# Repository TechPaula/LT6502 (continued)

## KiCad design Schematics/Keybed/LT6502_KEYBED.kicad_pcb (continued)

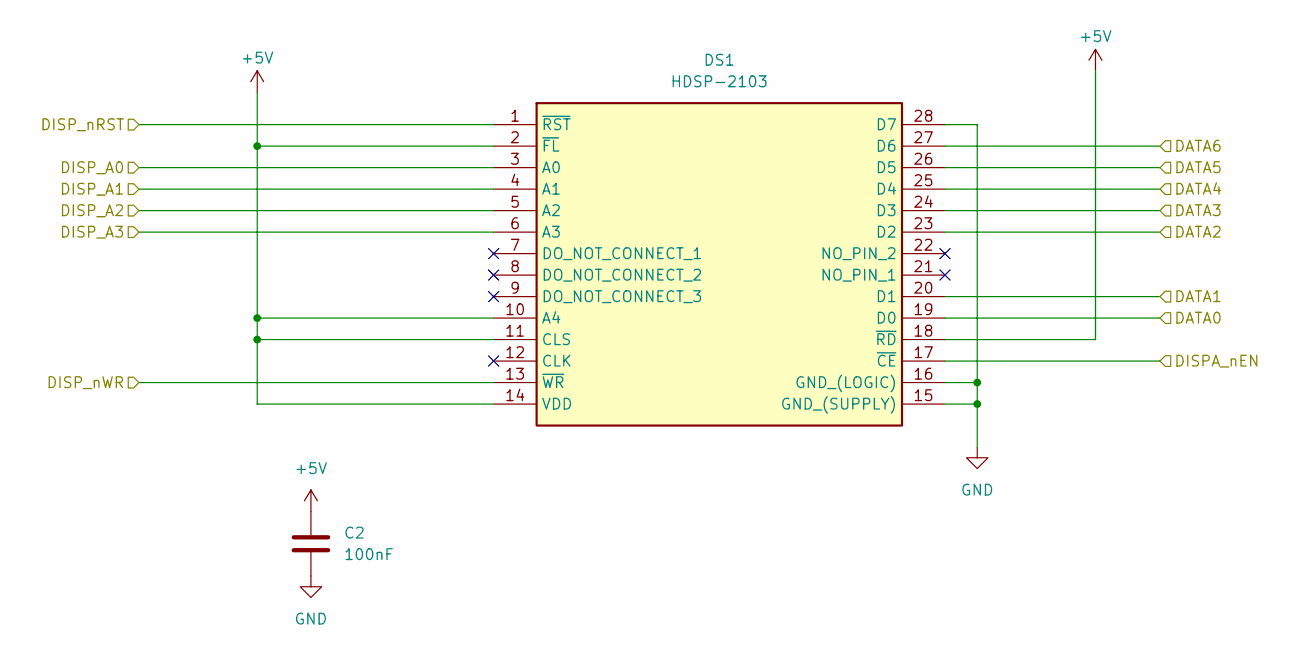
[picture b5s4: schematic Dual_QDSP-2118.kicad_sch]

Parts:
C2: 100nF; C_0805_2012Metric; LCSC C49678
DS1: HDSP-2103; DIPS1524W64P254L7087H685Q28N; Manufacturer_Part_Number HDSP-2503; Mouser Part Number 630-HDSP-2503

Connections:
+5V: C2.1, DS1.2 (~FL), DS1.10 (A4), DS1.11 (CLS), DS1.14 (VDD), DS1.18 (~RD); also elsewhere on the board
/DISPLAYs/DATA0: DS1.19 (D0); also elsewhere on the board
/DISPLAYs/DATA1: DS1.20 (D1); also elsewhere on the board
/DISPLAYs/DATA2: DS1.23 (D2); also elsewhere on the board
/DISPLAYs/DATA3: DS1.24 (D3); also elsewhere on the board
/DISPLAYs/DATA4: DS1.25 (D4); also elsewhere on the board
/DISPLAYs/DATA5: DS1.26 (D5); also elsewhere on the board
/DISPLAYs/DATA6: DS1.27 (D6); also elsewhere on the board
/DISPLAYs/DISPA_nEN: DS1.17 (~CE); also elsewhere on the board
/DISPLAYs/DISP_nRST: DS1.1 (~RST); also elsewhere on the board
/DISPLAYs/DISP_nWR: DS1.13 (~WR); also elsewhere on the board
AVR_TDO: DS1.6 (A3); also elsewhere on the board
DISP_A0: DS1.3 (A0); also elsewhere on the board
DISP_A1: DS1.4 (A1); also elsewhere on the board
DISP_A2: DS1.5 (A2); also elsewhere on the board
GND: C2.2, DS1.15 (GND_(SUPPLY)), DS1.16 (GND_(LOGIC)), DS1.28 (D7); also elsewhere on the board

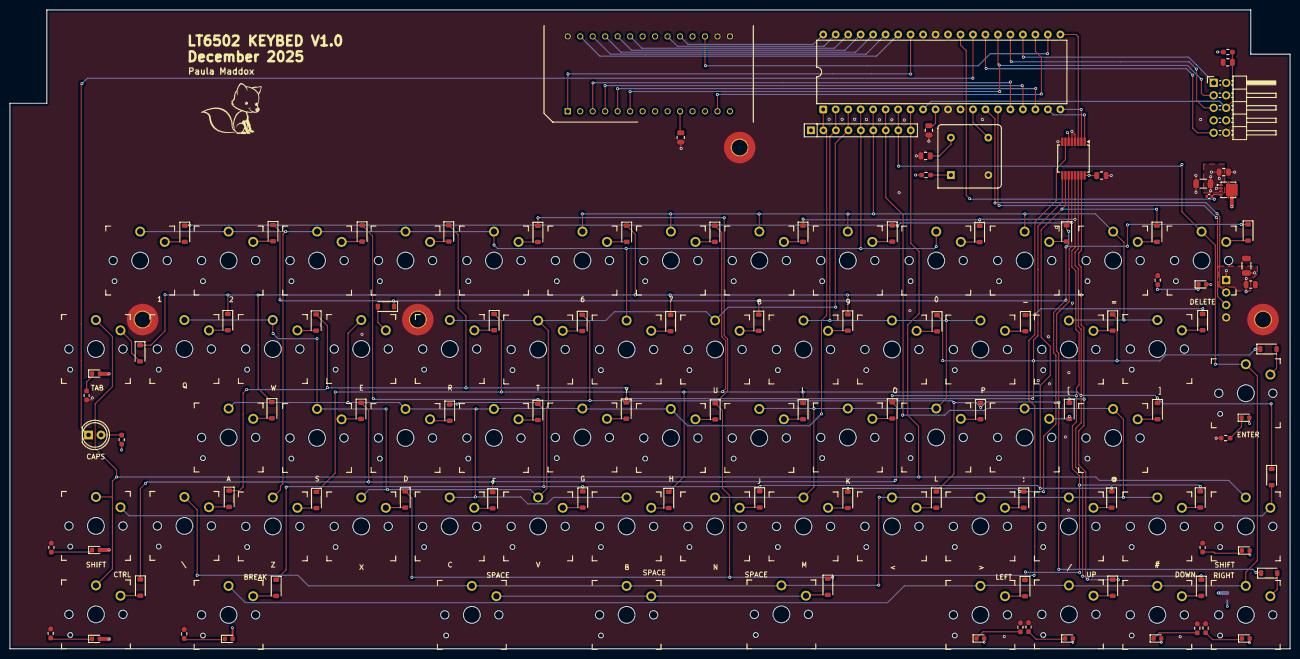
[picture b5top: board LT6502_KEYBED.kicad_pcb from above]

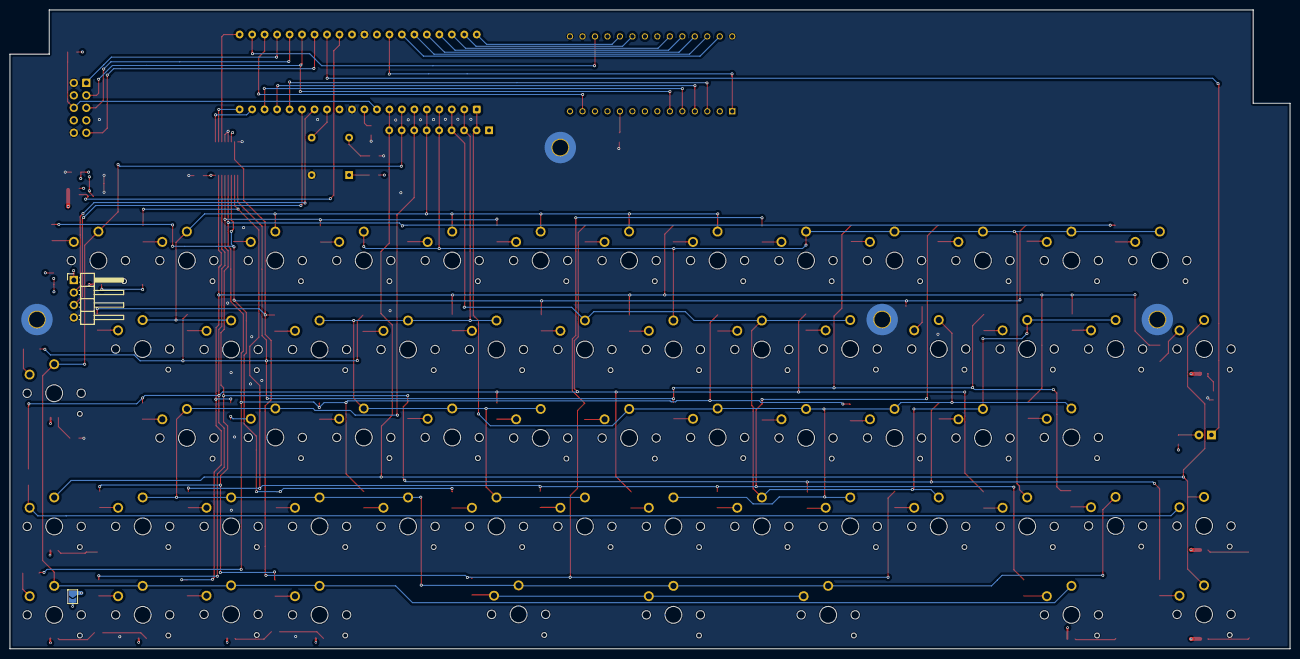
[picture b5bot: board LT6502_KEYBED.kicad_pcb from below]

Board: 4 copper layers, 260.5 x 130.0 mm, 169 parts (2 on the bottom side), 117 nets.

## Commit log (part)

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2025-11-12 Work in Progress
    Work in progress for Schematics and PCB
2025-11-12 Update README.md
    Added project info
2025-11-14 Tweaks to Schematics
    Shrunk main PCB
2025-11-15 Further work on Schematics, All parts placed on PCB
2025-12-14 Updated main board and started keybed
    main board a bit wider due to keybed width
    created keybed, begun routing
2025-12-17 Added speaker
    Added a simple LM386/speaker and link to CPLD for simple audio.
    Updated step files
2025-12-17 Routing Completed
    Routing completed, removed silkscreen IDs for clarity
2025-12-19 WIP images of case
2025-12-19 Updated step file for keybed
2025-12-19 edited PCB dimensions
    Loved LHS in 0.5mm to ensure it clears the case edge
2025-12-19 Early case design to test print
2025-12-20 Updated BoMs ordered PCBs
2025-12-20 Added render of case with lid
2025-12-23 added 1st expansion card
    Created a PCB and mocked up parts to check fit in case
2025-12-23 EXP card, updated PCB dimensions
2025-12-23 EXP Card, change to dimensions
    Brought dimensions in a little to ensure it fits within case.
2025-12-23 Added image of expansion slot
2025-12-26 Added first draft of display bezel
2025-12-26 Added test hinge
    Taken from here - https://www.printables.com/model/658393-friction-hinge-mechanism/comments#preview.file.aPNjd
2025-12-26 Added separate STL files for hinge
2025-12-26 Added my own hinge
2025-12-26 Compartment covers
2025-12-27 Case tweaks, rexport
2025-12-27 Updated Expansion board
2025-12-28 Added print files for final case.
2025-12-30 shorten expansion cover to fit
2025-12-30 Updated 3D prints, added BoM info
2025-12-31 Split Prints added BoM
    Split the base top (Keyboard surround) into it's own file to make printing easier.
    Added a list of parts needed for fixing the case together.
2025-12-31 Added light pipe holes
2025-12-31 Add power button
2025-12-31 added power button to print file
2026-01-02 First CPLD code
    ROM/RAM/Console sort of works, console only outputs when you send... odd... BUT it does work...
2026-01-03 Added STUSB4500 program for Teensy
    Simple bit of code to configure the STUSB4500 to request only 5V voltages from a USB-PD capable supply.
2026-01-03 Auto stash before merge of "main" and "origin/main"
2026-01-03 Simple CPLD Glue working
    Basic CPLD glue logic working with same memory mac as PC6502)
2026-01-03 CPLD code new memory map
    new memory map for CPLD code
2026-01-03 CPLD Glue
    Added 2nd RAM chip, extending the memory to almost 48K
2026-01-03 Firmware update
    Updated firmware (ROM) to fit new memory map and extra memory.
2026-01-03 Update progress
2026-01-03 Added shell scripts for making .bin to make my life easier :)
2026-01-03 Added enable for TXS0108 on data bus
2026-01-03 CPLD work and BASIC tests
    updated the CPLD with all chip selects
    Need to add remainder of control lines
    Also added some basic test programs
2026-01-03 Updated Schematic/PCB with comments
2026-01-03 Update README.md
    corrected mistake
2026-01-03 Updated memory map with beeper and gap
2026-01-04 Keyboard work
    Created BASIC test program
    Copied flash from PC6502 644P
2026-01-04 Updated Glue
2026-01-04 Updated ACIA test
2026-01-04 Keyboard integration
    Working on adding the keyboard input to the bootstrap
2026-01-05 Keyboard work/Images/schematic update
    min_mon.asm now has the required functions in to pass data from the keyboard TO basic!!
    I've added a few images of the build as I test things
    Added notes to Schematic
2026-01-05 Update README.md
    Added TODO list
2026-01-05 Working on code for keyboard
2026-01-05 updated keyboard prog script/tidy directory
2026-01-05 Updated Schematic/PCB
    Fixed battery connector polarity to save swapping wires.
2026-01-05 Keyboard code WIP
    Fixed Shift bug,
    Fixed flickering
    removed serial start message
    Removed junk first character out
2026-01-05 Expansion Template + Main Board update
    Created an expansion board template with main connector and correct PCB size
    Fixed bug with Charging circuit on main board that meant it wouldn't charge when off.
2026-01-08 Update README.md
    corrected spelling
2026-01-08 Added beeper test code
    Built and programmed main glue
    Added basic beeper test
2026-01-09 LED value change, added fix for FTDI power
2026-01-09 Update README.md
    Updated Display address range
2026-01-09 Working on CF
2026-01-09 glue logic work (CF/Beeper)
2026-01-09 working on CF write
    CF reading is fine, writing is not
2026-01-09 Added read of CF to CF_TEST
2026-01-09 sort issue with EXPansion select address
2026-01-09 CF now read/writing
    Compact flash test code now writes and reads.
2026-01-16 Moved eWoz and Minmon
    Moved ewoz and minmon so I have extra space in the IOHANDLER (min_mon) to add in routines to configure screen and output to it.
2026-01-16 PCB/Schematic edits
    moved speaker hole a little
    made nRES resistor for display no fit (this upsets them for some reason)
    Added diodes to ensure USB Console chip is powered when nothing attached (this causes issues with booting.
2026-01-16 More basic test programs
2026-01-18 Begun work on transputer expansion board
2026-01-18 Added place holder for display init on power on
2026-01-18 Work on case
2026-01-18 Added reset beeps
2026-01-18 Added slow0 for FTDI
    Had to add FT_CS to slow0 equation as it wouldn't always put characters onto the databus correctly
2026-01-18 Work on load/save
    Working on load/save, it now gets the number, as an integer, after the LOAD or SAVE command
2026-01-18 Glue edit
    trying to figure out why CF seems to cause errors
2026-01-18 work on display and CF
    new basic program that reads a sector of CF and displays it on the TFT
2026-01-18 New case printer files
2026-01-18 Updated comment as to why TXE and RXF were swapped, my bad
2026-01-20 Display debugging
    slight timing error on the "E" pulse meant that the 9" RA8875 did not work.
2026-01-22 Add DIR
    Added DIR to EhBASIC which calls a minmon function, currently just "beeps" but it works!
2026-01-22 New Mandelbrot (Pixel plot)
    plots 800x480 single pixel Mandelbrot with a nice colour scheme
2026-01-22 DIR command work
    made test program (basic) to wipe/read buffer memory
    successfully added DIR command which works from BASIC and dumps sector 0 of the CF into $0400-$05FF
    Needs more work to finish properly
2026-01-22 CF Read/Write work
    work on CF functions, improving reuse.
2026-01-22 Add display WAIT line to CPLD
    Display WAIT line can now be read from $BFD2 bit 3 (other bits are invalid)
2026-01-22 Tidy cpld
2026-01-23 Rework firmware
    Something went bad somewhere, replaced it all
2026-01-23 Glue update
    Updated Display pins and added missing logic
    Added simple SR latch for beeper.
2026-01-23 Found a bug with console input when Keyboard attached
    See comments on line 198 of min_mon.asm for outline of problem
2026-01-23 Console issue fix
    I've included the console select line in the SLOW0 logic, seems ok
2026-01-23 Updated Schematics
    Added bulk capacitance with higher ESR to help with display PLL starting
2026-01-23 GLUE updated to add DISP_nWT
    Added the DISP_nWT pin to D2 when read from the Display address+2 (or +3)
2026-01-23 Add display code to firmware
    Seems to work, on reset or boot, code configures the screen, clears the screen, sets text mode and homes the cursor.
    It also now outputs to the screen whatever is going to console.
    TODO: add in LF and CR handlerC #
    TODO: add in scrolling of text
2026-01-24 firmware work, add CLS/DIR and tidy CRLF
    Added place holder for new command DIR (just beeps)
    Added CLS command (clears LCD)
    tried to tidy some of the wasted space from excess CRLFs
2026-01-24 Added CLS to console Mandelbrot
    also changed scaling to fit more on the screen
2026-01-24 Updated current limits
    Updated the current limits as we were pushing the previous limit (900mA) with display, keyboard and CF
2026-01-25 added LOW beep for error/add TODO list
2026-01-25 Removed excess code now it's in firmware
2026-01-25 Added MODE to basic
    MODE 0 is text
    MODE 1 is graphics
    Anything else results in TEXT MODE
    Added handling in EhBASIC so errors drop to text mode first.
2026-01-25 Added switch graphics mode
2026-01-26 FIXED BROKEN TOKENS
    Fixed the broken tokens for basic commands caused by adding new commands in the wrong place.
    HOWEVER symbols (= + - * / etc) are now broken
2026-01-26 working on BTE move, test program (not working)
2026-01-27 Fixed issue with tokens
    Found the issue with the tokens being wrong, it's subtle, but new commands MUST be in the same order for the TK_ as they are in LAB_KEYT
2026-01-27 Scrolling on text screen working!
    HUGE thank you to Paul Dourish, without his work this wouldn't hae been possible.
2026-01-30 tidy mandelbrot code add new code
2026-01-30 Fix CLS when doing LIST
2026-01-30 Added beep
    Added variable pitch beep, slimmed down power on and error beeps
    only works with immediate values for now
2026-01-30 replace CALL with BEEP command
2026-01-30 BEEP command now works with immediate and variables
    I found the issue thanks to this video - https://www.youtube.com/watch?v=kTbxUGV5qtQ
    I needed to use LAB_GTBY *and* do a TXA!
2026-01-30 New base lower, base top and power button
2026-01-31 Now doesn't ask for memory size
2026-01-31 Added start banner and LF to eWozmon
    Added LF to ewozmon whenever a CR is sent, output also now goes to LCD
2026-01-31 Added keyboard input to eWozmon
    also tidied wozmon tabs/spacing
2026-01-31 Added WOZMON to BASIC and COLOUR command
    calling WOZMON from in basic jumps to WOZMON, to exit use "Q"
2026-01-31 Added colour to start banner just for fun
2026-01-31 Created text colour mandelbrot
    Same colour scheme as the pixel based one :)
2026-01-31 PLOT XXXX,YYYY,CCC command added
2026-01-31 Replaced long gosubs with PLOT command
2026-01-31 minor edit to colourtext mandelbrot
2026-01-31 begun reducing size of some functions
2026-01-31 Added circle command
    CIRCLE XXXX,YYYY,RR,CC,F
2026-01-31 Remove loops
2026-02-01 Updated and added BASIC examples
2026-02-02 added OUTK command
    OUTK sends a string/value to the display on the keyboard
2026-02-02 Tinkering with loop increments
2026-02-02 saved lower case .3MF file
2026-02-04 Updated case parts (lower)
    Updated case top/bottom/button and expansion cover
2026-02-06 Create screen and hinge parts
2026-02-07 SAVE & LOAD WORK
    Saving and loading of programs under 512 bytes seems to work
2026-02-07 LOAD & SAVE WORKING
    Load and save using JUST a "slot" number works!!
2026-02-07 Save now saves name upto 16 characters
2026-02-07 LOAD now shows name of program it's loading
2026-02-07 Added load error for blank slot
2026-02-07 DIR added
    DIR works, added a "format" program for the SDCard
2026-02-08 Update README.md
    Added list of commands
2026-02-08 Changed limit for DIR
    DIR now scans the first 2048 Slots only, it takes too long to do more.
2026-02-08 Updated BASIC programs
2026-02-08 Added Image
2026-02-08 Update README.md
    Added images
2026-02-08 Updated parts for lid
2026-02-08 Updated 3D print files.
2026-02-09 Update README.md
    Fixed dates
2026-02-11 Resolve issue with Lid Hinge part
2026-02-11 Work on hinge parts
2026-02-11 Updated Hinge & front bezel
2026-02-13 Added LINE and SQUARE commands
2026-02-13 Added more basic test files
2026-02-13 Added TRIANGLE to BASIC
2026-02-13 Updated BASIC test programs
2026-02-14 Updated print files and added photos of assembled unit
2026-02-15 Added duration to BEEP command
2026-02-16 added CURSOR command
    this moves the CURSOR X,Y where X & y are columns and rows
    Also added a "tick" and beep for DIR/LOAD/SAVE
2026-02-16 Added progmini.sh to make EEPROM
2026-02-16 correct CURSOR X/Y orientation
2026-02-16 game of life (seems VERY slow)
2026-02-21 Work on Expansion card
    I keep changing my mind what is on this, so who knows.
2026-02-21 Maths hat BASIC code
